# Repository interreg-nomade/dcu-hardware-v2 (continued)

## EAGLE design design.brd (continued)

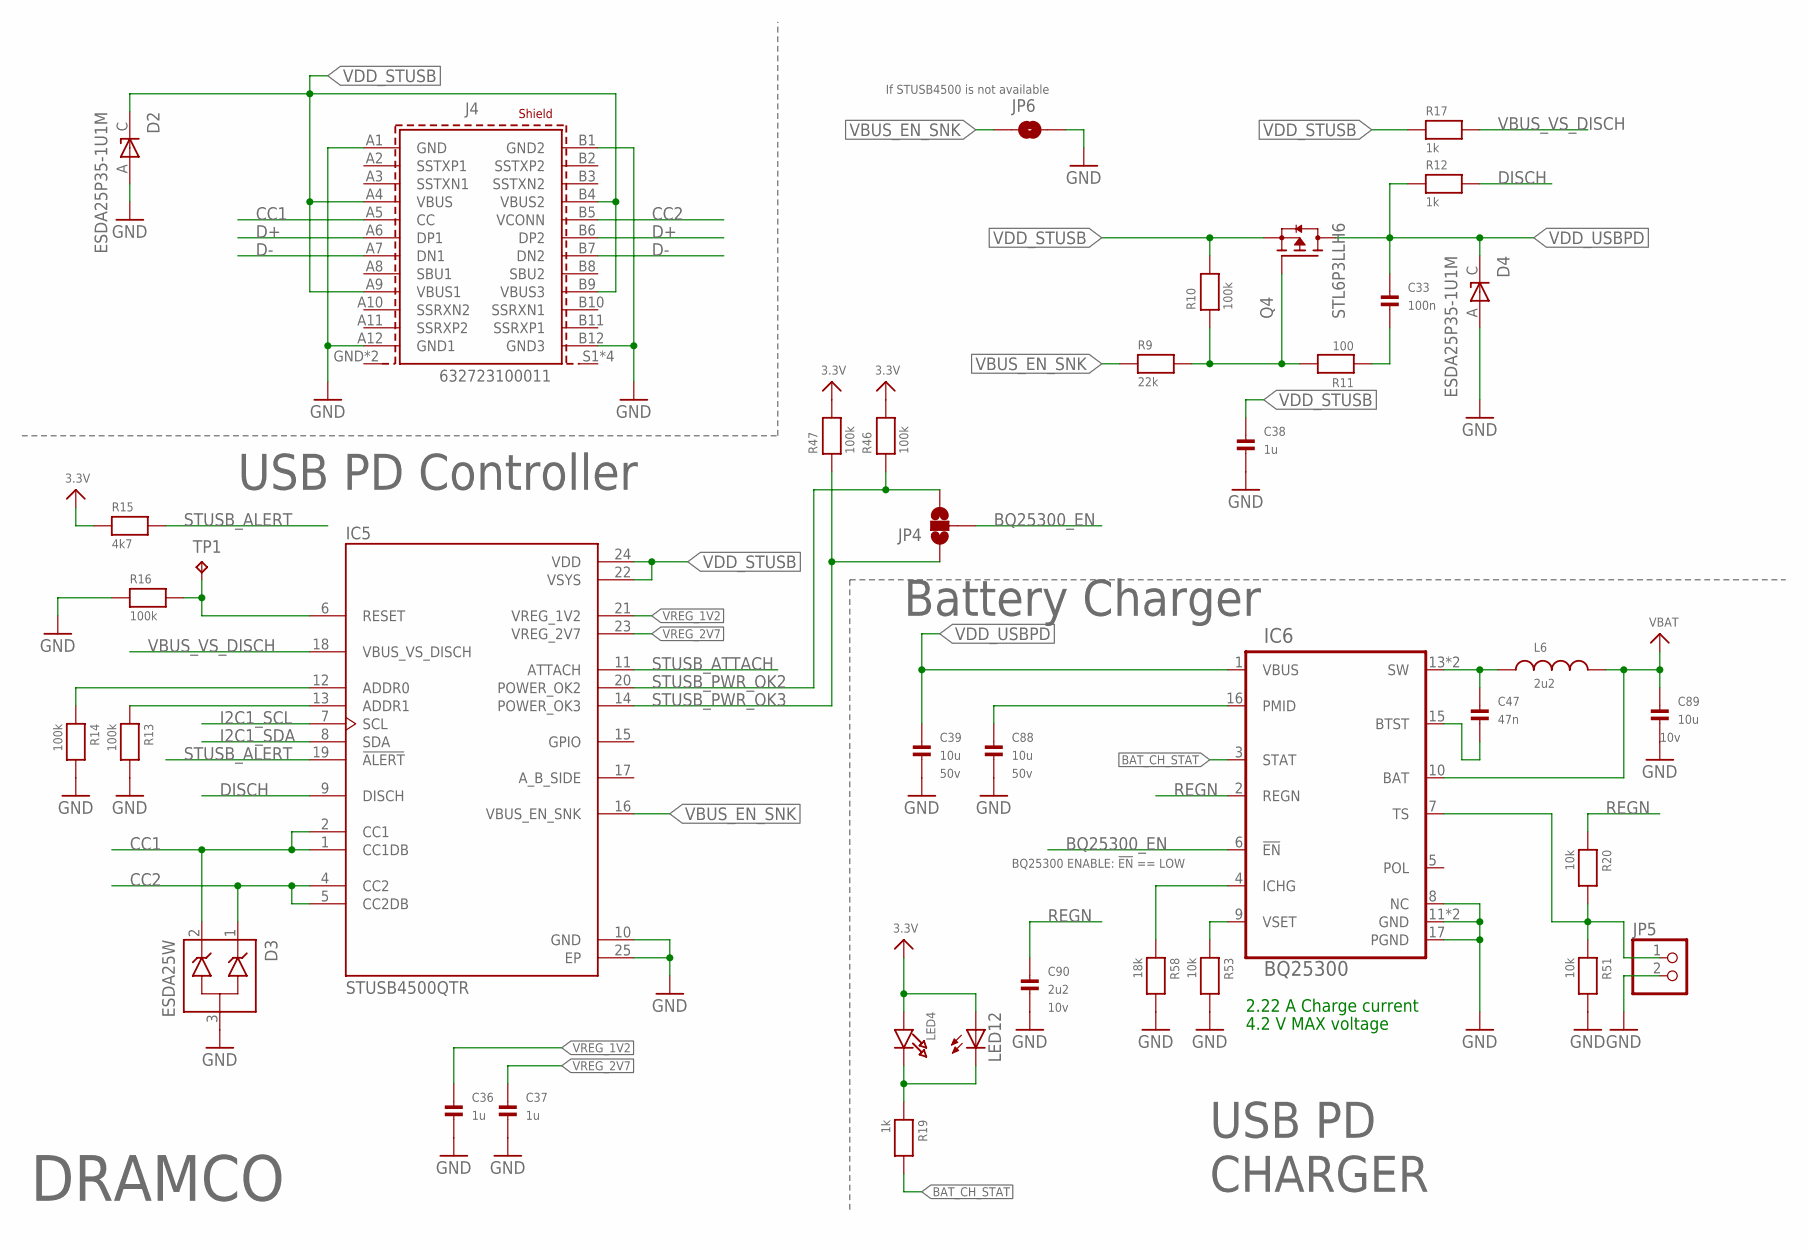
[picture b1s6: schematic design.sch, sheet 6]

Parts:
C33: 100n; 0603
C36, C37: 1u; 0603
C38: 1u; 0805
C39, C88: 10u; 1206
C47: 47n; 0603
C89: 10u; 0805
C90: 2u2; 0603
D2, D4: ESDA25P35-1U1M; TVS_ESDA25P35-1U1M
D3: ESDA25W; SOT65P210X110-3N
IC5: STUSB4500QTR; QFN50P400X400X90-25N
IC6: BQ25300; QFN50P350X350X100-21N
J4: 632723100011
JP4: JUMPER-SMT_3_NO_NO-SILK; SMT-JUMPER_3_NO_NO-SILK
JP5: HEADER-1X2ROUND; 1X02_ROUND
JP6: JUMPER-SMT_2_NO_NO-SILK; SMT-JUMPER_2_NO_NO-SILK
L6: 2u2; WE-MAIA_3020
LED4: LED0805; CHIPLED_0805
LED12: LED3MM
Q4: STL6P3LLH6; TRANS_STL6P3LLH6
R9: 22k; 0603
R10, R13, R14, R16, R46, R47: 100k; 0603
R11: 100; 0603
R12, R17, R19: 1k; 0603
R15: 4k7; 0603
R20, R51, R53: 10k; 0603
R58: 18k; 0603
TP1: TPTP10R; TP10R

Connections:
3.3V: LED4.A, LED12.A, R15.1, R46.2, R47.2; also elsewhere on the board
BAT_CH_STAT: IC6.3 (STAT), R19.2; also elsewhere on the board
BQ25300_EN: IC6.6 (!EN), JP4.2
CC1: D3.2 (C2), IC5.1 (CC1DB), IC5.2 (CC1), J4.A5 (CC)
CC2: D3.1 (C1), IC5.4 (CC2), IC5.5 (CC2DB), J4.B5 (VCONN)
D+: J4.A6 (DP1), J4.B6 (DP2); also elsewhere on the board
D-: J4.A7 (DN1), J4.B7 (DN2); also elsewhere on the board
DISCH: IC5.9 (DISCH), R12.2
GND: C36.2, C37.2, C38.2, C39.2, C88.2, C89.2, C90.2, D2.A, D3.3 (CA), D4.A, IC5.10 (GND), IC5.25 (EP), IC6.8 (NC), IC6.11 (GND), IC6.12 (GND), IC6.17 (PGND), J4.A1 (GND), J4.A12 (GND1), J4.B1 (GND2), J4.B12 (GND3), JP5.2, JP6.2, R13.2, R14.2, R16.1, R51.2, R53.2, R58.2; also elsewhere on the board
I2C1_SCL: IC5.7 (SCL); also elsewhere on the board
I2C1_SDA: IC5.8 (SDA); also elsewhere on the board
unnamed: IC5.13 (ADDR1), R13.1
unnamed: C33.2, R11.1
unnamed: Q4.4 (G), R9.2, R10.1, R11.2
unnamed: IC5.12 (ADDR0), R14.1
unnamed: IC5.6 (RESET), R16.2, TP1.TP
unnamed: IC6.9 (VSET), R53.1
unnamed: IC6.4 (ICHG), R58.1
unnamed: LED4.C, LED12.K (C), R19.1
unnamed: C47.2, IC6.15 (BTST)
unnamed: C88.1, IC6.16 (PMID)
unnamed: C47.1, IC6.13 (SW), IC6.14 (SW), L6.1
unnamed: IC6.7 (TS), JP5.1, R20.2, R51.1
REGN: C90.1, IC6.2 (REGN), R20.1
STUSB_ALERT: IC5.19 (!ALERT), R15.2; also elsewhere on the board
STUSB_ATTACH: IC5.11 (ATTACH); also elsewhere on the board
STUSB_PWR_OK2: IC5.20 (POWER_OK2), JP4.3, R46.1; also elsewhere on the board
STUSB_PWR_OK3: IC5.14 (POWER_OK3), JP4.1, R47.1; also elsewhere on the board
VBAT: C89.1, IC6.10 (BAT), L6.2; also elsewhere on the board
VBUS_EN_SNK: IC5.16 (VBUS_EN_SNK), JP6.1, R9.1
VBUS_VS_DISCH: IC5.18 (VBUS_VS_DISCH), R17.2
VDD_STUSB: C38.1, D2.C, IC5.22 (VSYS), IC5.24 (VDD), J4.A4 (VBUS), J4.A9 (VBUS1), J4.B4 (VBUS2), J4.B9 (VBUS3), Q4.1 (S), Q4.2 (S), Q4.3 (S), R10.2, R17.1; also elsewhere on the board
VDD_USBPD: C33.1, C39.1, D4.C, IC6.1 (VBUS), Q4.5_8 (D), R12.1
VREG_1V2: C36.1, IC5.21 (VREG_1V2)
VREG_2V7: C37.1, IC5.23 (VREG_2V7)

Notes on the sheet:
DRAMCO
50v
BQ25300 ENABLE: !EN! == LOW
10v
USB PD CHARGER
2.22 A Charge current
4.2 V MAX voltage
USB PD Controller
Battery Charger
If STUSB4500 is not available

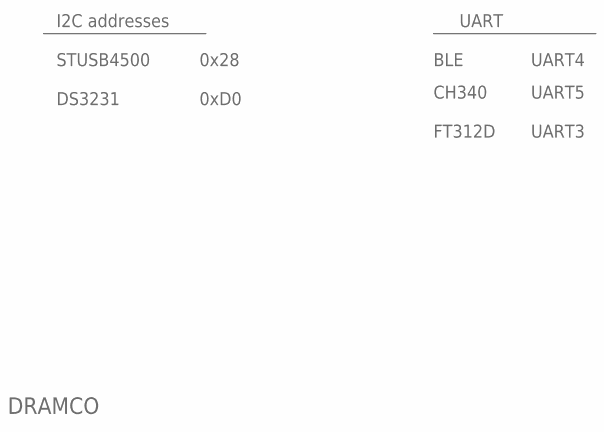
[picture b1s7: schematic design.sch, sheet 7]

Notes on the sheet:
DRAMCO
I2C addresses
STUSB4500
DS3231
0x28
0xD0
UART
UART4
BLE
CH340
UART5
UART3
FT312D

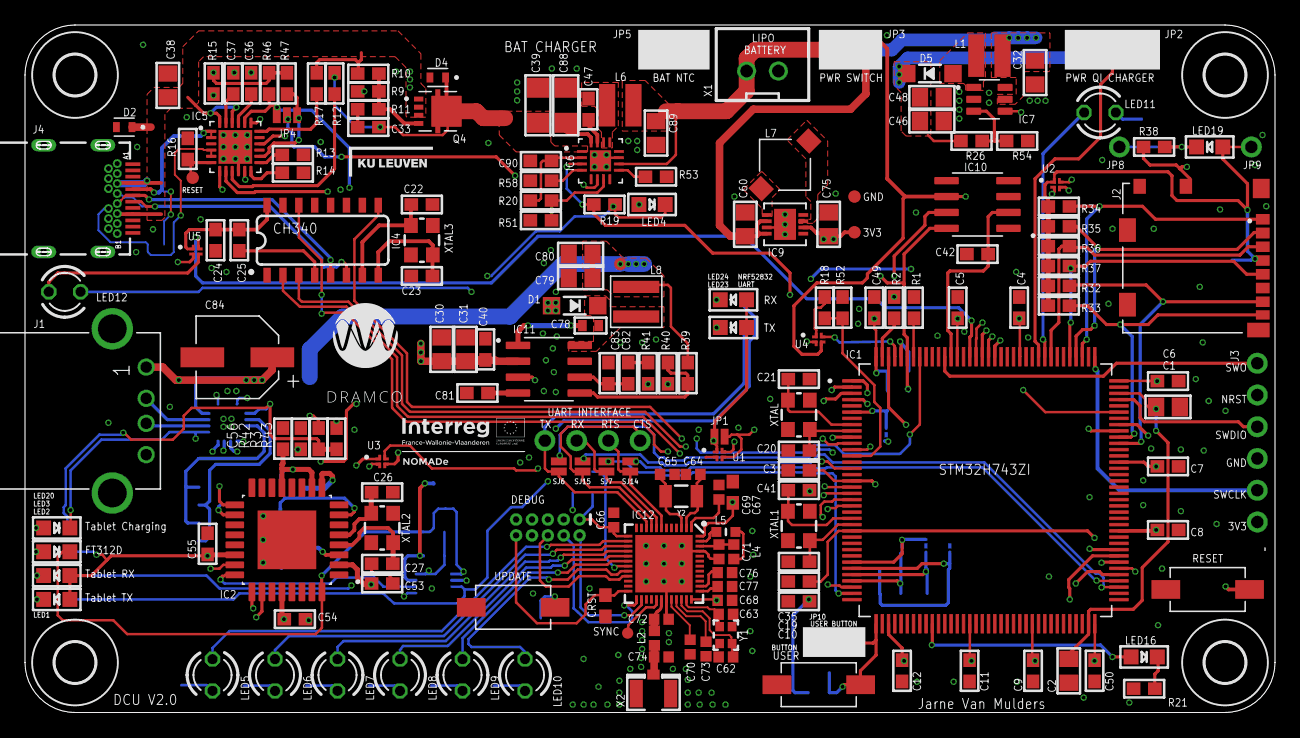
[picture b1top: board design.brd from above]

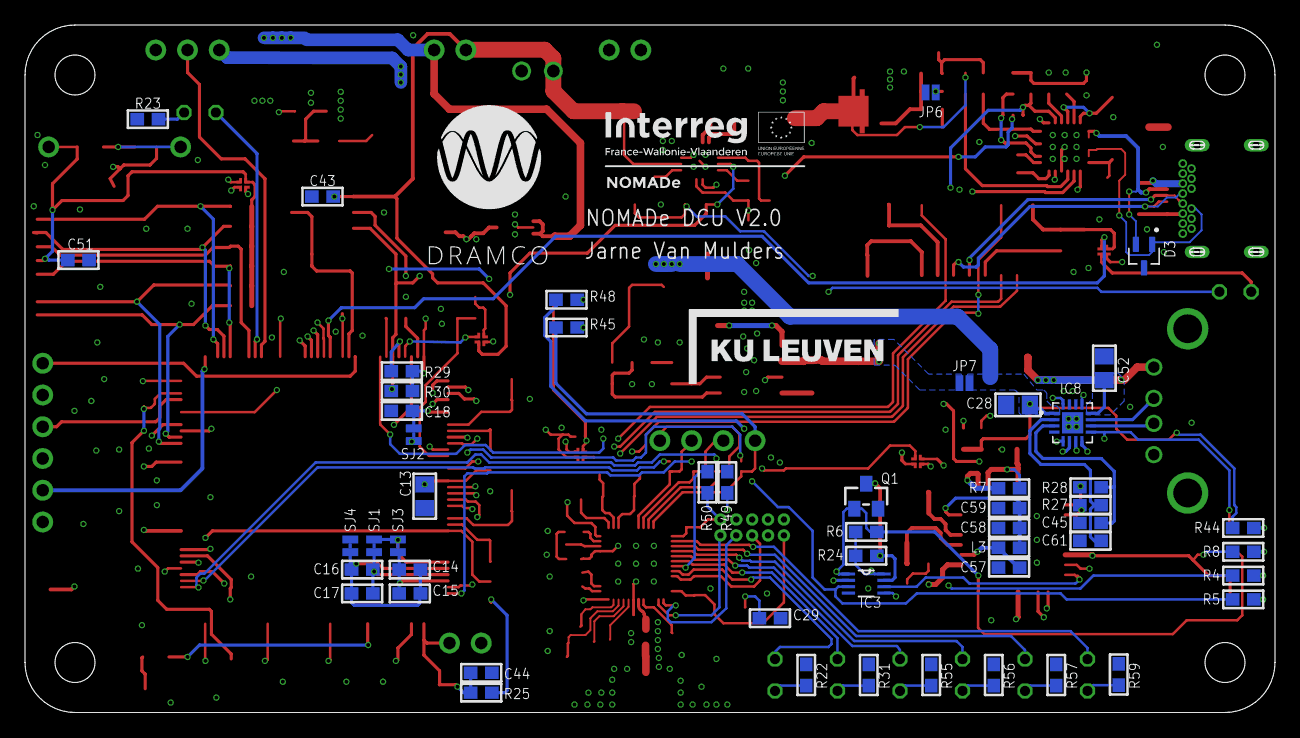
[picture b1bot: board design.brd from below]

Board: 4 copper layers, 99.9 x 54.9 mm, 239 parts (51 on the bottom side), 171 nets.

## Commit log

2021-06-29 Init commit
